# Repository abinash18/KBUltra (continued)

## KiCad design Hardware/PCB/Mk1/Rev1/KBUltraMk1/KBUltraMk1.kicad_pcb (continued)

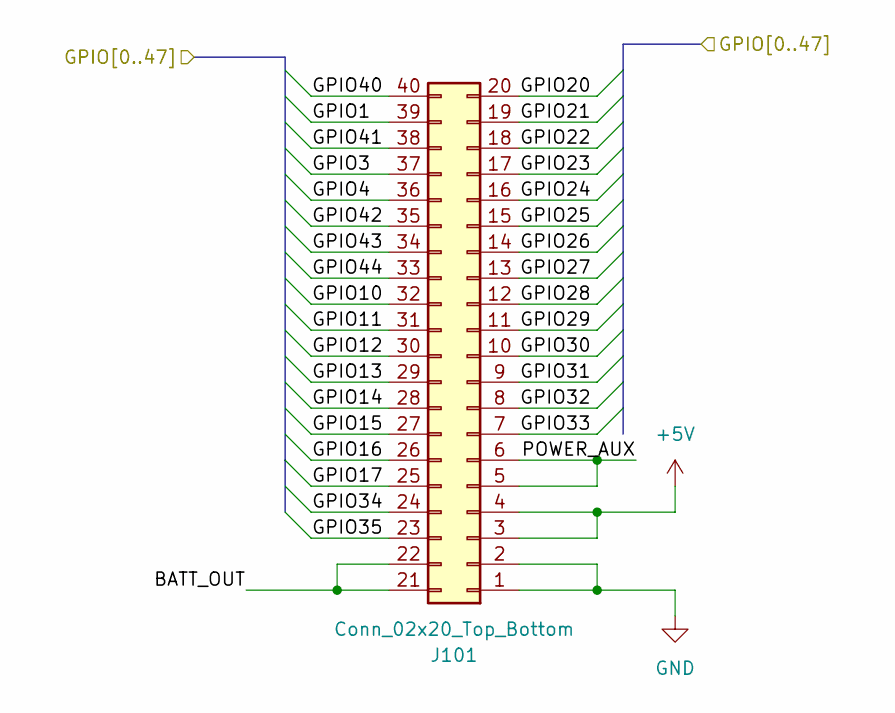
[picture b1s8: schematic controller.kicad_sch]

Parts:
J101: Conn_02x20_Top_Bottom; PinHeader_2x20_P2.54mm_Vertical

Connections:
+5V: J101.3, J101.4; also elsewhere on the board
/Controller/BATT_OUT: J101.21, J101.22
/Controller/GPIO1: J101.39; also elsewhere on the board
/Controller/GPIO3: J101.37; also elsewhere on the board
/Controller/GPIO4: J101.36; also elsewhere on the board
/Controller/GPIO10: J101.32; also elsewhere on the board
/Controller/GPIO11: J101.31; also elsewhere on the board
/Controller/GPIO12: J101.30; also elsewhere on the board
/Controller/GPIO13: J101.29; also elsewhere on the board
/Controller/GPIO14: J101.28; also elsewhere on the board
/Controller/GPIO15: J101.27; also elsewhere on the board
/Controller/GPIO16: J101.26; also elsewhere on the board
/Controller/GPIO17: J101.25; also elsewhere on the board
/Controller/GPIO20: J101.20; also elsewhere on the board
/Controller/GPIO21: J101.19; also elsewhere on the board
/Controller/GPIO22: J101.18; also elsewhere on the board
/Controller/GPIO23: J101.17; also elsewhere on the board
/Controller/GPIO24: J101.16; also elsewhere on the board
/Controller/GPIO25: J101.15; also elsewhere on the board
/Controller/GPIO26: J101.14; also elsewhere on the board
/Controller/GPIO27: J101.13; also elsewhere on the board
/Controller/GPIO28: J101.12; also elsewhere on the board
/Controller/GPIO29: J101.11; also elsewhere on the board
/Controller/GPIO30: J101.10; also elsewhere on the board
/Controller/GPIO31: J101.9; also elsewhere on the board
/Controller/GPIO32: J101.8; also elsewhere on the board
/Controller/GPIO33: J101.7; also elsewhere on the board
/Controller/GPIO34: J101.24; also elsewhere on the board
/Controller/GPIO35: J101.23; also elsewhere on the board
/Controller/GPIO40: J101.40; also elsewhere on the board
/Controller/GPIO41: J101.38; also elsewhere on the board
/Controller/GPIO42: J101.35; also elsewhere on the board
/Controller/GPIO43: J101.34; also elsewhere on the board
/Controller/GPIO44: J101.33; also elsewhere on the board
/Controller/POWER_AUX: J101.5, J101.6
GND: J101.1, J101.2; also elsewhere on the board

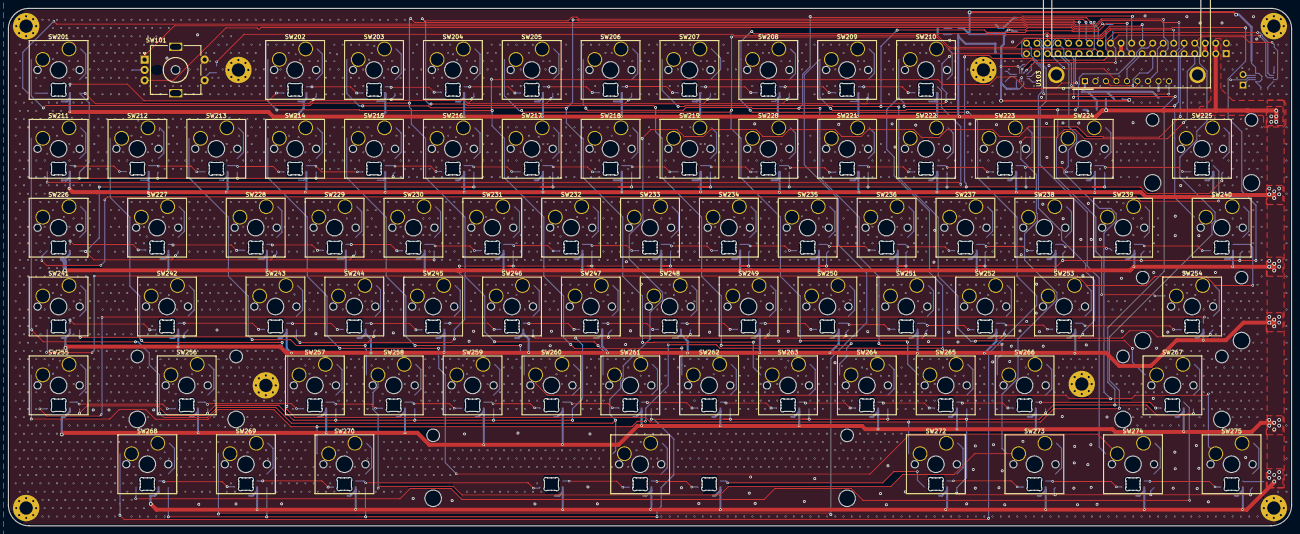
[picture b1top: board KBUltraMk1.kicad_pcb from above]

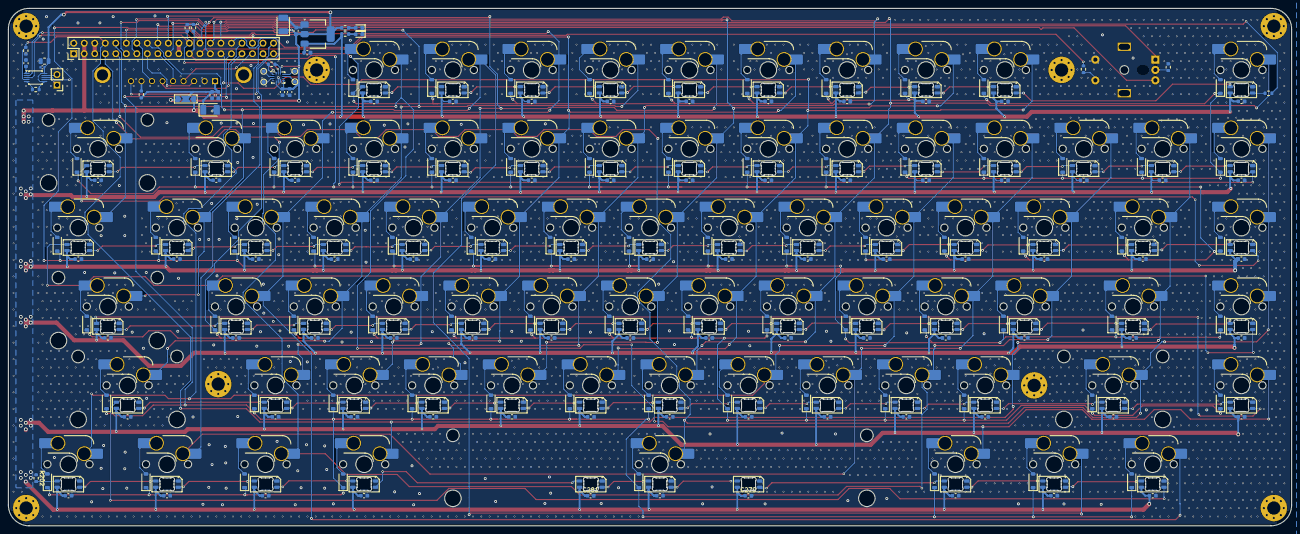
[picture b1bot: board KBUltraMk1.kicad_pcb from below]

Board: 2 copper layers, 310.0 x 125.0 mm, 354 parts (264 on the bottom side), 205 nets.

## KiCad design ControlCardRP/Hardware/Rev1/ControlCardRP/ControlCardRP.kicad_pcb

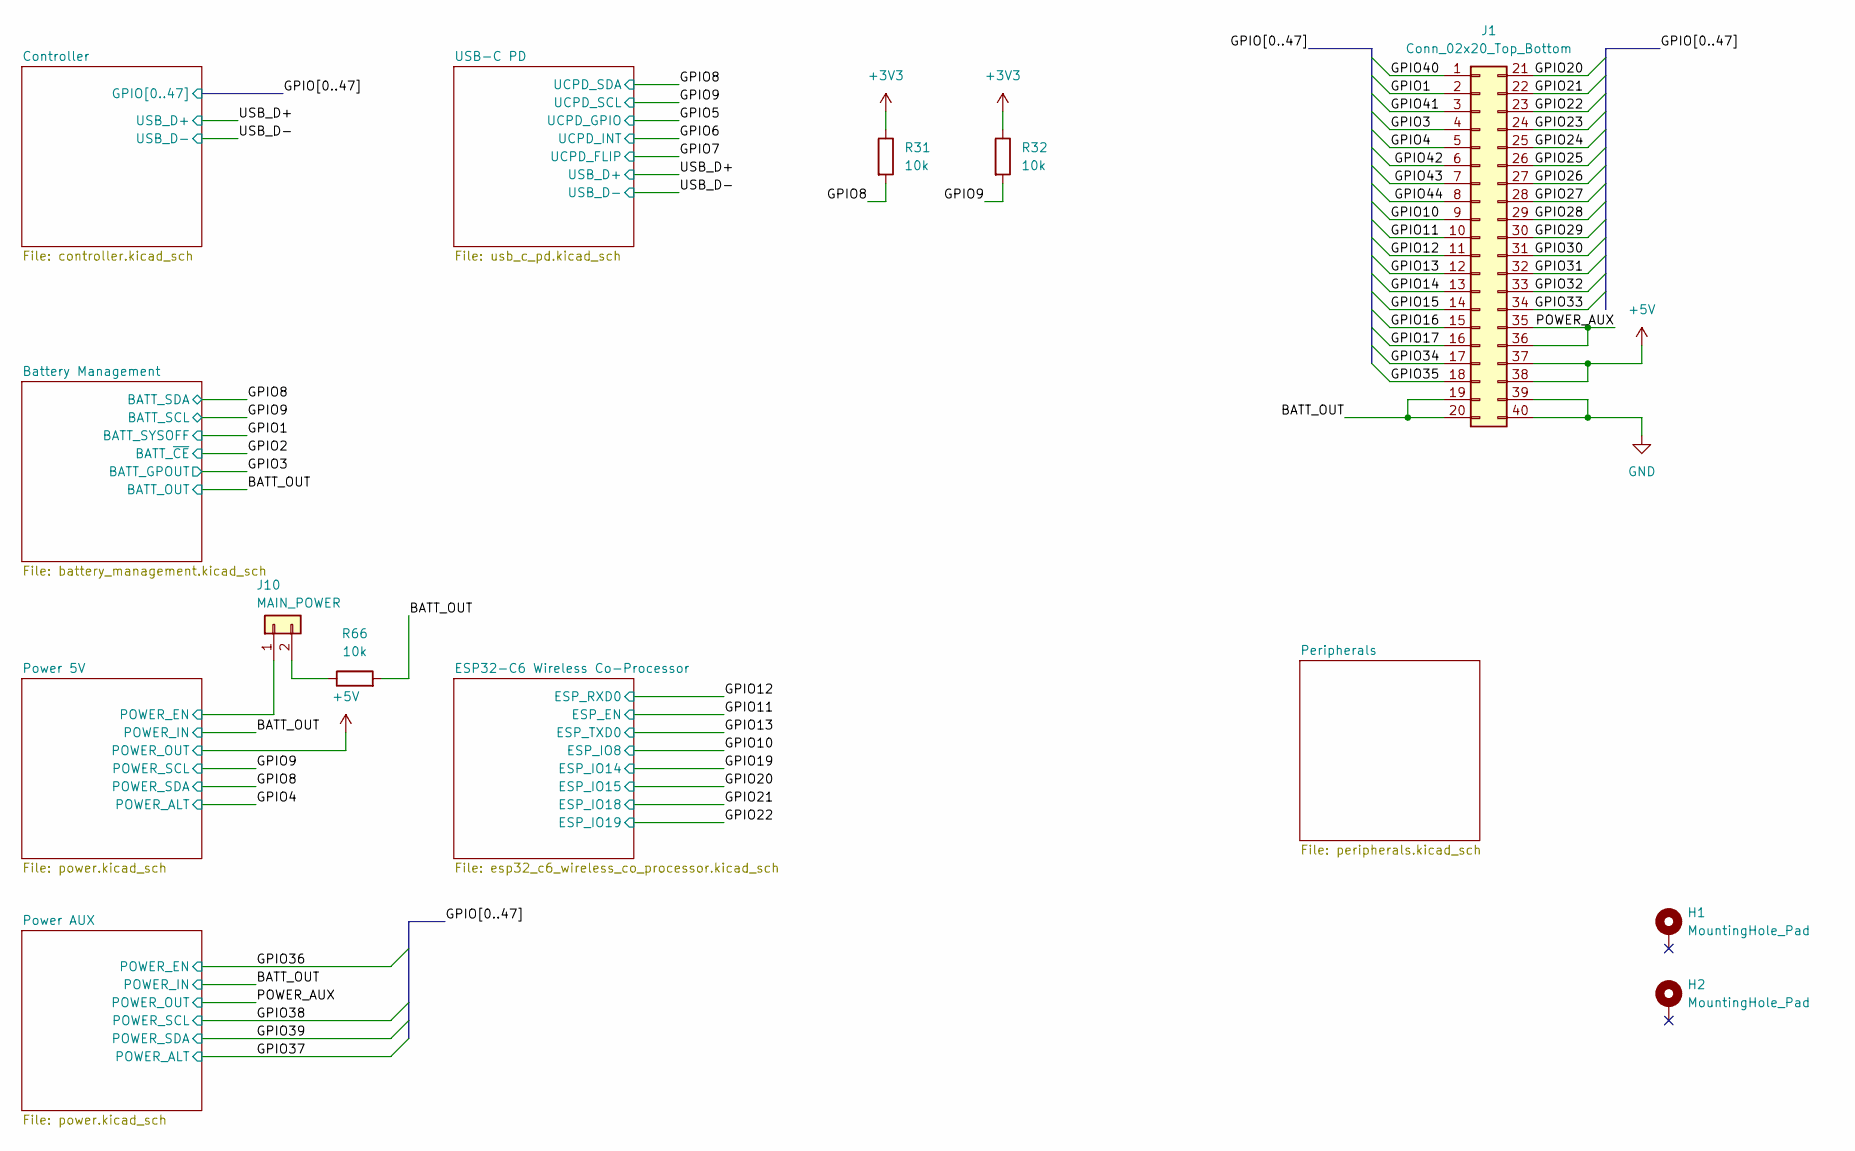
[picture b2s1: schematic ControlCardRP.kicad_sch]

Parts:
H1, H2: MountingHole_Pad; MountingHole_3.2mm_M3_Pad_Via
J1: Conn_02x20_Top_Bottom; PinSocket_2x20_P2.54mm_Vertical_SMD
J10: MAIN_POWER; PinHeader_1x02_P2.54mm_Vertical
R31, R32, R66: 10k; R_0402_1005Metric; LCSC Part # C25744

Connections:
+3V3: R31.1, R32.1; also elsewhere on the board
+5V: J1.37, J1.38; also elsewhere on the board
/BATT_OUT: J1.19, J1.20, R66.2; also elsewhere on the board
/GPIO1: J1.2; also elsewhere on the board
/GPIO3: J1.4; also elsewhere on the board
/GPIO4: J1.5; also elsewhere on the board
/GPIO8: R31.2; also elsewhere on the board
/GPIO9: R32.2; also elsewhere on the board
/GPIO10: J1.9; also elsewhere on the board
/GPIO11: J1.10; also elsewhere on the board
/GPIO12: J1.11; also elsewhere on the board
/GPIO13: J1.12; also elsewhere on the board
/GPIO14: J1.13; also elsewhere on the board
/GPIO15: J1.14; also elsewhere on the board
/GPIO16: J1.15; also elsewhere on the board
/GPIO17: J1.16; also elsewhere on the board
/GPIO20: J1.21; also elsewhere on the board
/GPIO21: J1.22; also elsewhere on the board
/GPIO22: J1.23; also elsewhere on the board
/GPIO23: J1.24; also elsewhere on the board
/GPIO24: J1.25; also elsewhere on the board
/GPIO25: J1.26; also elsewhere on the board
/GPIO26: J1.27; also elsewhere on the board
/GPIO27: J1.28; also elsewhere on the board
/GPIO28: J1.29; also elsewhere on the board
/GPIO29: J1.30; also elsewhere on the board
/GPIO30: J1.31; also elsewhere on the board
/GPIO31: J1.32; also elsewhere on the board
/GPIO32: J1.33; also elsewhere on the board
/GPIO33: J1.34; also elsewhere on the board
/GPIO34: J1.17; also elsewhere on the board
/GPIO35: J1.18; also elsewhere on the board
/GPIO40: J1.1; also elsewhere on the board
/GPIO41: J1.3; also elsewhere on the board
/GPIO42: J1.6; also elsewhere on the board
/GPIO43: J1.7; also elsewhere on the board
/GPIO44: J1.8; also elsewhere on the board
/POWER_AUX: J1.35, J1.36; also elsewhere on the board
/Power 5V/POWER_EN: J10.1; also elsewhere on the board
GND: J1.39, J1.40; also elsewhere on the board
unnamed: J10.2, R66.1

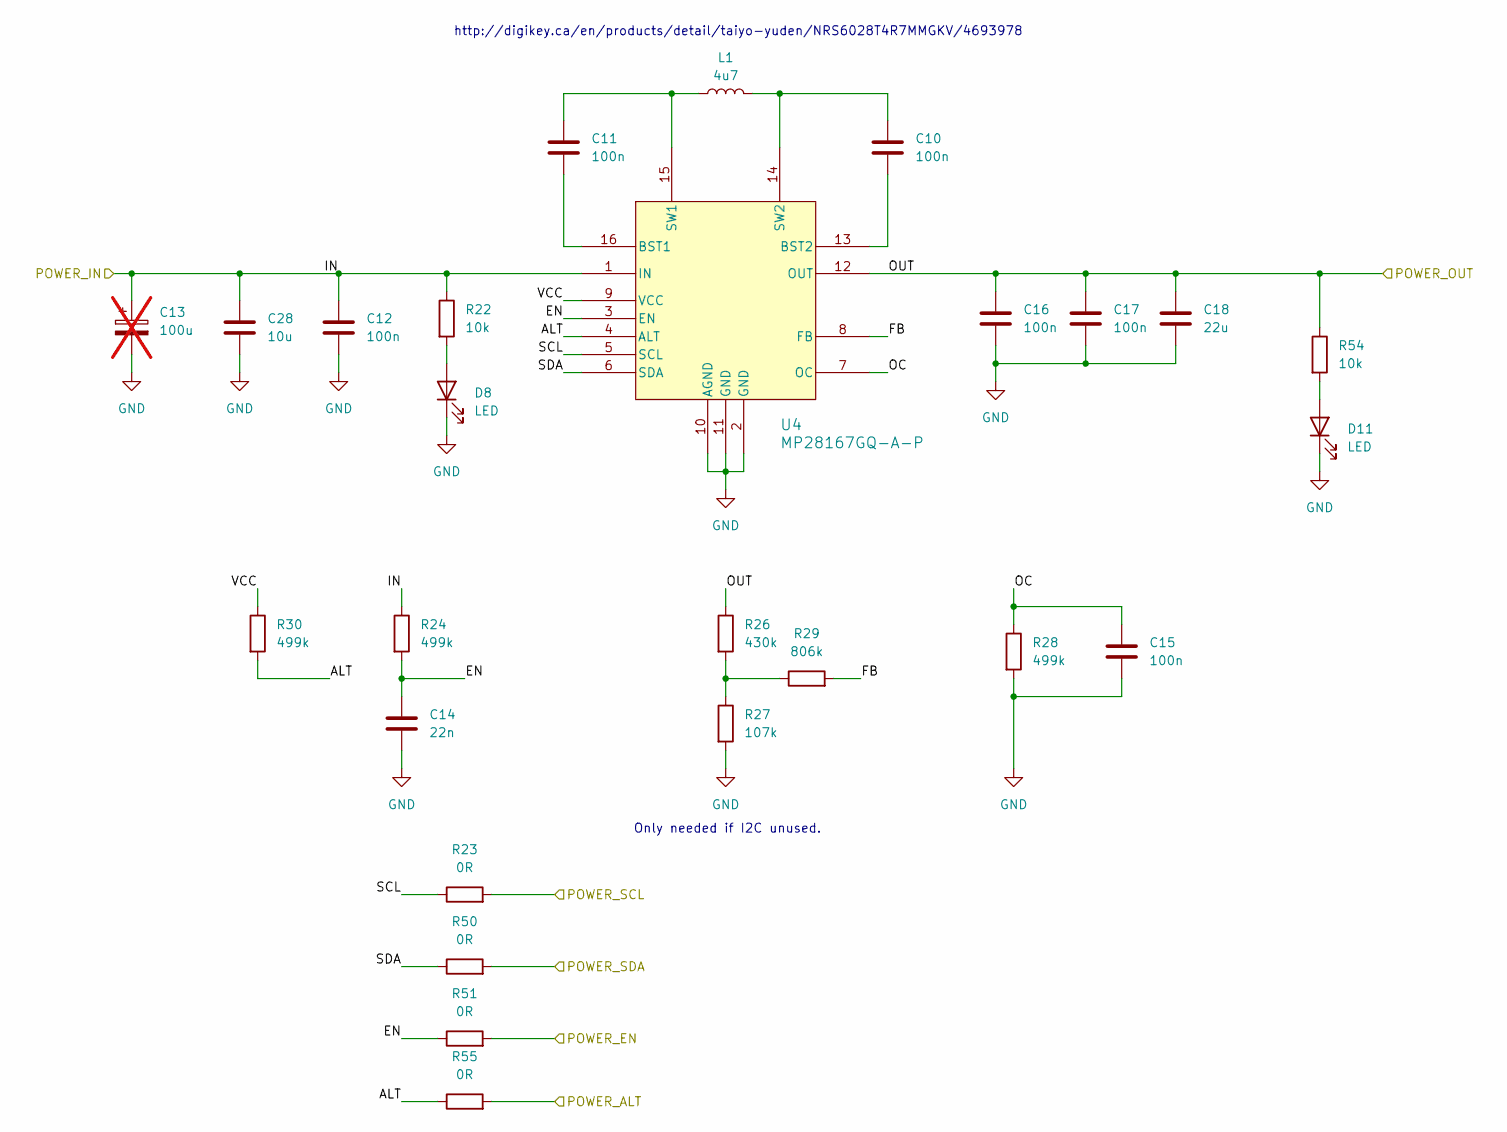
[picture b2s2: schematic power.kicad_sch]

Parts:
C10, C11, C12, C16, C17: 100n; C_0402_1005Metric; LCSC Part # C307331
C13: 100u; CP_Elec_5x5.4; not fitted
C14: 22n; C_0402_1005Metric; LCSC Part # C1532
C15: 100n; C_0402_1005Metric; LCSC Part # C1525
C18: 22u; C_1206_3216Metric; LCSC Part # C12891
C28: 10u; C_0603_1608Metric; LCSC Part # C96446
D8, D11: LED; LED_0603_1608Metric
L1: 4u7; L_Taiyo-Yuden_NR-60xx
R22, R54: 10k; R_0402_1005Metric; LCSC Part # C25744
R23, R50, R51, R55: 0R; R_0402_1005Metric; LCSC Part # C17168
R24, R28, R30: 499k; R_0402_1005Metric; LCSC Part # C25778
R26: 430k; R_0603_1608Metric; LCSC Part # C25969
R27: 107k; R_0603_1608Metric; LCSC Part # C25805
R29: 806k; R_0603_1608Metric; LCSC Part # C23240
U4: MP28167GQ-A-P; QFN-16_MP28167_MNP

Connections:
+5V: C16.1, C17.1, C18.1, R26.1, R54.1, U4.12 (OUT); also elsewhere on the board
/BATT_OUT: C12.1, C13.1, C28.1, R22.1, R24.1, U4.1 (IN); also elsewhere on the board
/GPIO4: R55.2; also elsewhere on the board
/GPIO8: R50.2; also elsewhere on the board
/GPIO9: R23.2; also elsewhere on the board
/Power 5V/ALT: R30.2, R55.1, U4.4 (ALT)
/Power 5V/EN: C14.1, R24.2, R51.1, U4.3 (EN)
/Power 5V/FB: R29.2, U4.8 (FB)
/Power 5V/OC: C15.1, R28.1, U4.7 (OC)
/Power 5V/POWER_EN: R51.2; also elsewhere on the board
/Power 5V/SCL: R23.1, U4.5 (SCL)
/Power 5V/SDA: R50.1, U4.6 (SDA)
/Power 5V/VCC: R30.1, U4.9 (VCC)
GND: C12.2, C13.2, C14.2, C15.2, C16.2, C17.2, C18.2, C28.2, D8.1 (K), D11.1 (K), R27.2, R28.2, U4.2 (GND), U4.10 (AGND), U4.11 (GND); also elsewhere on the board
unnamed: D8.2 (A), R22.2
unnamed: D11.2 (A), R54.2
unnamed: R26.2, R27.1, R29.1
unnamed: C11.2, U4.16 (BST1)
unnamed: C10.2, U4.13 (BST2)
unnamed: C11.1, L1.1, U4.15 (SW1)
unnamed: C10.1, L1.2, U4.14 (SW2)

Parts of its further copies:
C26: 100u; CP_Elec_5x5.4; not fitted
C27, C31, C32, C33, C34: 100n; C_0402_1005Metric; LCSC Part # C307331
C29: 10u; C_0603_1608Metric; LCSC Part # C96446
C30: 22n; C_0402_1005Metric; LCSC Part # C1532
C35: 100n; C_0402_1005Metric; LCSC Part # C1525
C36: 22u; C_1206_3216Metric; LCSC Part # C12891
D9, D12: LED; LED_0603_1608Metric
L2: 4u7; L_Taiyo-Yuden_NR-60xx
R52, R53, R64: 499k; R_0402_1005Metric; LCSC Part # C25778
R56, R65: 10k; R_0402_1005Metric; LCSC Part # C25744
R57, R58, R59, R60: 0R; R_0402_1005Metric; LCSC Part # C17168
R61: 430k; R_0603_1608Metric; LCSC Part # C25969
R62: 107k; R_0603_1608Metric; LCSC Part # C25805
R63: 806k; R_0603_1608Metric; LCSC Part # C23240
U8: MP28167GQ-A-P; QFN-16_MP28167_MNP

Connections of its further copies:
/BATT_OUT: C26.1, C27.1, C29.1, R53.1, R56.1, U8.1 (IN); also elsewhere on the board
/GPIO36: R59.2; also elsewhere on the board
/GPIO37: R60.2; also elsewhere on the board
/GPIO38: R57.2; also elsewhere on the board
/GPIO39: R58.2; also elsewhere on the board
/POWER_AUX: C33.1, C34.1, C36.1, R61.1, R65.1, U8.12 (OUT); also elsewhere on the board
/Power AUX/ALT: R52.2, R60.1, U8.4 (ALT)
/Power AUX/EN: C30.1, R53.2, R59.1, U8.3 (EN)
/Power AUX/FB: R63.2, U8.8 (FB)
/Power AUX/OC: C35.1, R64.1, U8.7 (OC)
/Power AUX/SCL: R57.1, U8.5 (SCL)
/Power AUX/SDA: R58.1, U8.6 (SDA)
/Power AUX/VCC: R52.1, U8.9 (VCC)
GND: C26.2, C27.2, C29.2, C30.2, C33.2, C34.2, C35.2, C36.2, D9.1 (K), D12.1 (K), R62.2, R64.2, U8.2 (GND), U8.10 (AGND), U8.11 (GND); also elsewhere on the board
unnamed: D9.2 (A), R56.2
unnamed: D12.2 (A), R65.2
unnamed: R61.2, R62.1, R63.1
unnamed: C31.2, U8.16 (BST1)
unnamed: C32.2, U8.13 (BST2)
unnamed: C31.1, L2.1, U8.15 (SW1)
unnamed: C32.1, L2.2, U8.14 (SW2)

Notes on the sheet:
http://digikey.ca/en/products/detail/taiyo-yuden/NRS6028T4R7MMGKV/4693978
Only needed if I2C unused.

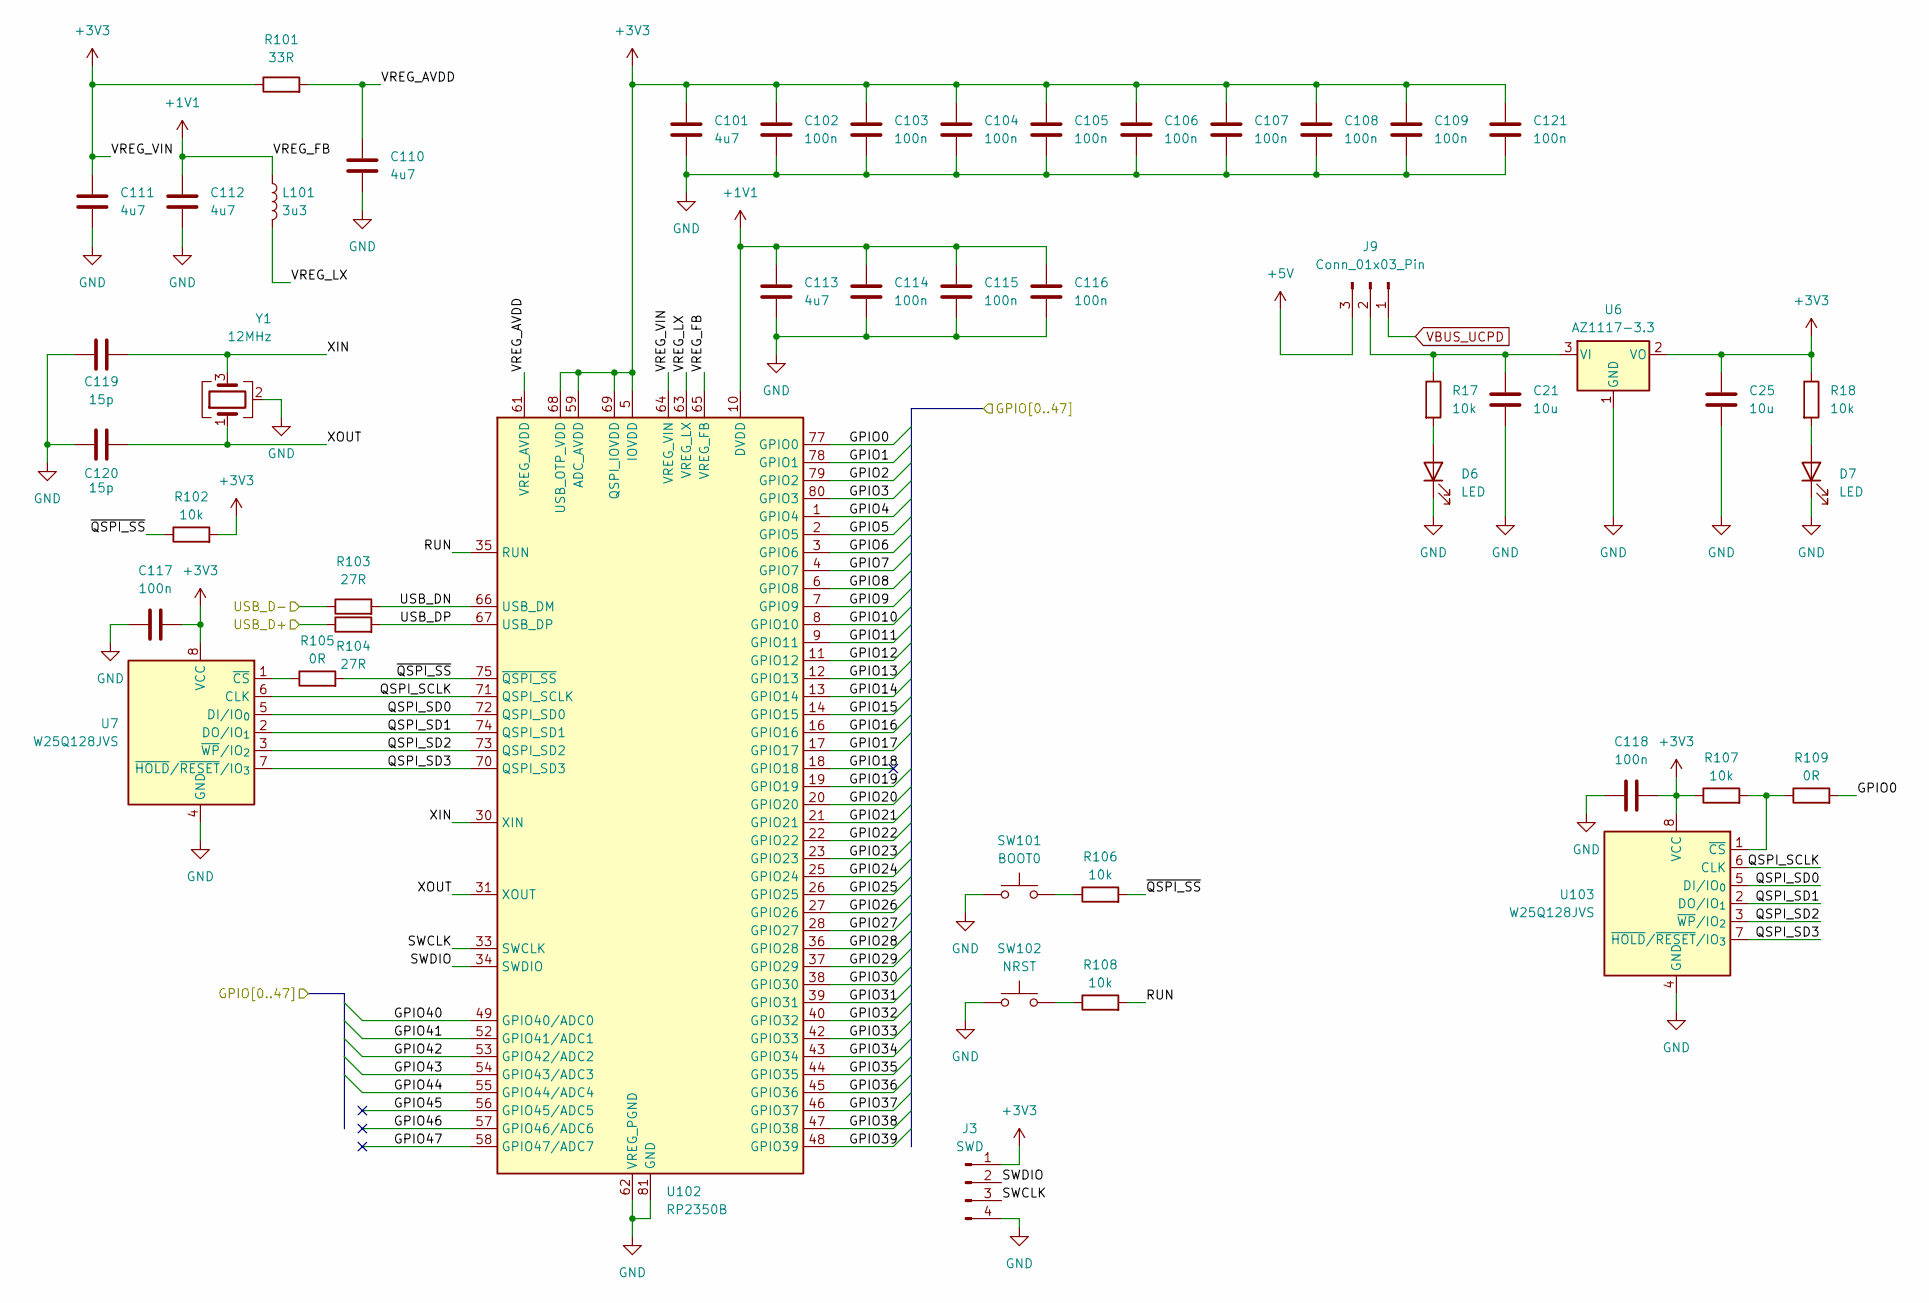
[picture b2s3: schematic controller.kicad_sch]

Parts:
C21, C25: 10u; C_0603_1608Metric; LCSC Part # C96446
C101, C110, C111, C112, C113: 4u7; C_0402_1005Metric; LCSC Part # C23733
C102, C103, C104, C105, C106, C107, C108, C109, C114, C115, C116, C117, C118, C121: 100n; C_0402_1005Metric; LCSC Part # C1525
C119, C120: 15p; C_0402_1005Metric; LCSC Part # C1548
D6, D7: LED; LED_0603_1608Metric
J3: SWD; PinHeader_1x04_P2.54mm_Vertical
J9: Conn_01x03_Pin; PinHeader_1x03_P1.27mm_Vertical
L101: 3u3; AOTA-B201610S3R3-101-T
R17, R18, R102, R106, R107, R108: 10k; R_0402_1005Metric; LCSC Part # C25744
R101: 33R; R_0402_1005Metric; LCSC Part # C25105
R103, R104: 27R; R_0603_1608Metric; LCSC Part # C25190
R105, R109: 0R; R_0402_1005Metric; LCSC Part # C17168
SW101: BOOT0; SW_SPST_PTS810
SW102: NRST; SW_SPST_PTS810
U6: AZ1117-3.3; SOT-89-3
U7, U103: W25Q128JVS; SOIC-8_5.3x5.3mm_P1.27mm
U102: RP2350B; QFN-80-1EP_10x10mm_P0.4mm_EP3.4x3.4mm
Y1: 12MHz; Crystal_SMD_3225-4Pin_3.2x2.5mm

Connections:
+1V1: C112.1, C113.1, C114.1, C115.1, C116.1, L101.1, U102.10 (DVDD), U102.32 (DVDD), U102.51 (DVDD), U102.65 (VREG_FB)
+3V3: C25.1, C101.1, C102.1, C103.1, C104.1, C105.1, C106.1, C107.1, C108.1, C109.1, C111.1, C117.2, C118.2, C121.1, J3.1, R18.1, R101.1, R102.2, R107.1, U6.2 (VO), U7.8 (VCC), U102.5 (IOVDD), U102.15 (IOVDD), U102.24 (IOVDD), U102.29 (IOVDD), U102.41 (IOVDD), U102.50 (IOVDD), U102.59 (ADC_AVDD), U102.60 (IOVDD), U102.64 (VREG_VIN), U102.68 (USB_OTP_VDD), U102.69 (QSPI_IOVDD), U102.76 (IOVDD), U103.8 (VCC); also elsewhere on the board
+5V: J9.3; also elsewhere on the board
/Controller/QSPI_SCLK: U7.6 (CLK), U102.71 (QSPI_SCLK), U103.6 (CLK)
/Controller/QSPI_SD0: U7.5 (DI/IO_{0}), U102.72 (QSPI_SD0), U103.5 (DI/IO_{0})
/Controller/QSPI_SD1: U7.2 (DO/IO_{1}), U102.74 (QSPI_SD1), U103.2 (DO/IO_{1})
/Controller/QSPI_SD2: U7.3 (~WP/IO_{2}), U102.73 (QSPI_SD2), U103.3 (~WP/IO_{2})
/Controller/QSPI_SD3: U7.7 (~HOLD/~RESET/IO_{3}), U102.70 (QSPI_SD3), U103.7 (~HOLD/~RESET/IO_{3})
/Controller/RUN: R108.2, U102.35 (RUN)
/Controller/SWCLK: J3.3, U102.33 (SWCLK)
/Controller/SWDIO: J3.2, U102.34 (SWDIO)
/Controller/USB_DN: R103.2, U102.66 (USB_DM)
/Controller/USB_DP: R104.2, U102.67 (USB_DP)
/Controller/VREG_AVDD: C110.1, R101.2, U102.61 (VREG_AVDD)
/Controller/VREG_LX: L101.2, U102.63 (VREG_LX)
/Controller/XIN: C119.2, U102.30 (XIN), Y1.3
/Controller/XOUT: C120.1, U102.31 (XOUT), Y1.1
/Controller/~QSPI_SS: R102.1, R105.2, R106.2, U102.75 (~QSPI_SS)
/GPIO0: R109.2, U102.77 (GPIO0)
/GPIO1: U102.78 (GPIO1); also elsewhere on the board
/GPIO2: U102.79 (GPIO2); also elsewhere on the board
/GPIO3: U102.80 (GPIO3); also elsewhere on the board
/GPIO4: U102.1 (GPIO4); also elsewhere on the board
/GPIO5: U102.2 (GPIO5); also elsewhere on the board
/GPIO6: U102.3 (GPIO6); also elsewhere on the board
/GPIO7: U102.4 (GPIO7); also elsewhere on the board
/GPIO8: U102.6 (GPIO8); also elsewhere on the board
/GPIO9: U102.7 (GPIO9); also elsewhere on the board
/GPIO10: U102.8 (GPIO10); also elsewhere on the board
/GPIO11: U102.9 (GPIO11); also elsewhere on the board
/GPIO12: U102.11 (GPIO12); also elsewhere on the board
/GPIO13: U102.12 (GPIO13); also elsewhere on the board
/GPIO14: U102.13 (GPIO14); also elsewhere on the board
/GPIO15: U102.14 (GPIO15); also elsewhere on the board
/GPIO16: U102.16 (GPIO16); also elsewhere on the board
/GPIO17: U102.17 (GPIO17); also elsewhere on the board
/GPIO18: U102.18 (GPIO18)
/GPIO19: U102.19 (GPIO19); also elsewhere on the board
/GPIO20: U102.20 (GPIO20); also elsewhere on the board
/GPIO21: U102.21 (GPIO21); also elsewhere on the board
/GPIO22: U102.22 (GPIO22); also elsewhere on the board
/GPIO23: U102.23 (GPIO23); also elsewhere on the board
/GPIO24: U102.25 (GPIO24); also elsewhere on the board
/GPIO25: U102.26 (GPIO25); also elsewhere on the board
/GPIO26: U102.27 (GPIO26); also elsewhere on the board
/GPIO27: U102.28 (GPIO27); also elsewhere on the board
/GPIO28: U102.36 (GPIO28); also elsewhere on the board
/GPIO29: U102.37 (GPIO29); also elsewhere on the board
/GPIO30: U102.38 (GPIO30); also elsewhere on the board
/GPIO31: U102.39 (GPIO31); also elsewhere on the board
/GPIO32: U102.40 (GPIO32); also elsewhere on the board
/GPIO33: U102.42 (GPIO33); also elsewhere on the board
/GPIO34: U102.43 (GPIO34); also elsewhere on the board
/GPIO35: U102.44 (GPIO35); also elsewhere on the board
/GPIO36: U102.45 (GPIO36); also elsewhere on the board
/GPIO37: U102.46 (GPIO37); also elsewhere on the board
/GPIO38: U102.47 (GPIO38); also elsewhere on the board
/GPIO39: U102.48 (GPIO39); also elsewhere on the board
/GPIO40: U102.49 (GPIO40/ADC0); also elsewhere on the board
/GPIO41: U102.52 (GPIO41/ADC1); also elsewhere on the board
/GPIO42: U102.53 (GPIO42/ADC2); also elsewhere on the board
/GPIO43: U102.54 (GPIO43/ADC3); also elsewhere on the board
/GPIO44: U102.55 (GPIO44/ADC4); also elsewhere on the board
/GPIO45: U102.56 (GPIO45/ADC5)
/GPIO46: U102.57 (GPIO46/ADC6)
/GPIO47: U102.58 (GPIO47/ADC7)
/USB_D+: R104.1; also elsewhere on the board
/USB_D-: R103.1; also elsewhere on the board
GND: C21.2, C25.2, C101.2, C102.2, C103.2, C104.2, C105.2, C106.2, C107.2, C108.2, C109.2, C110.2, C111.2, C112.2, C113.2, C114.2, C115.2, C116.2, C117.1, C118.1, C119.1, C120.2, C121.2, D6.1 (K), D7.1 (K), J3.4, SW101.1, SW102.1, U6.1 (GND), U7.4 (GND), U102.62 (VREG_PGND), U102.81 (GND), U103.4 (GND), Y1.2 (G), Y1.4 (G); also elsewhere on the board
unnamed: D6.2 (A), R17.2
unnamed: D7.2 (A), R18.2
unnamed: C21.1, J9.2, R17.1, U6.3 (VI)
unnamed: R106.1, SW101.2
unnamed: R108.1, SW102.2
unnamed: R105.1, U7.1 (~CS)
unnamed: R107.2, R109.1, U103.1 (~CS)
VBUS_UCPD: J9.1; also elsewhere on the board

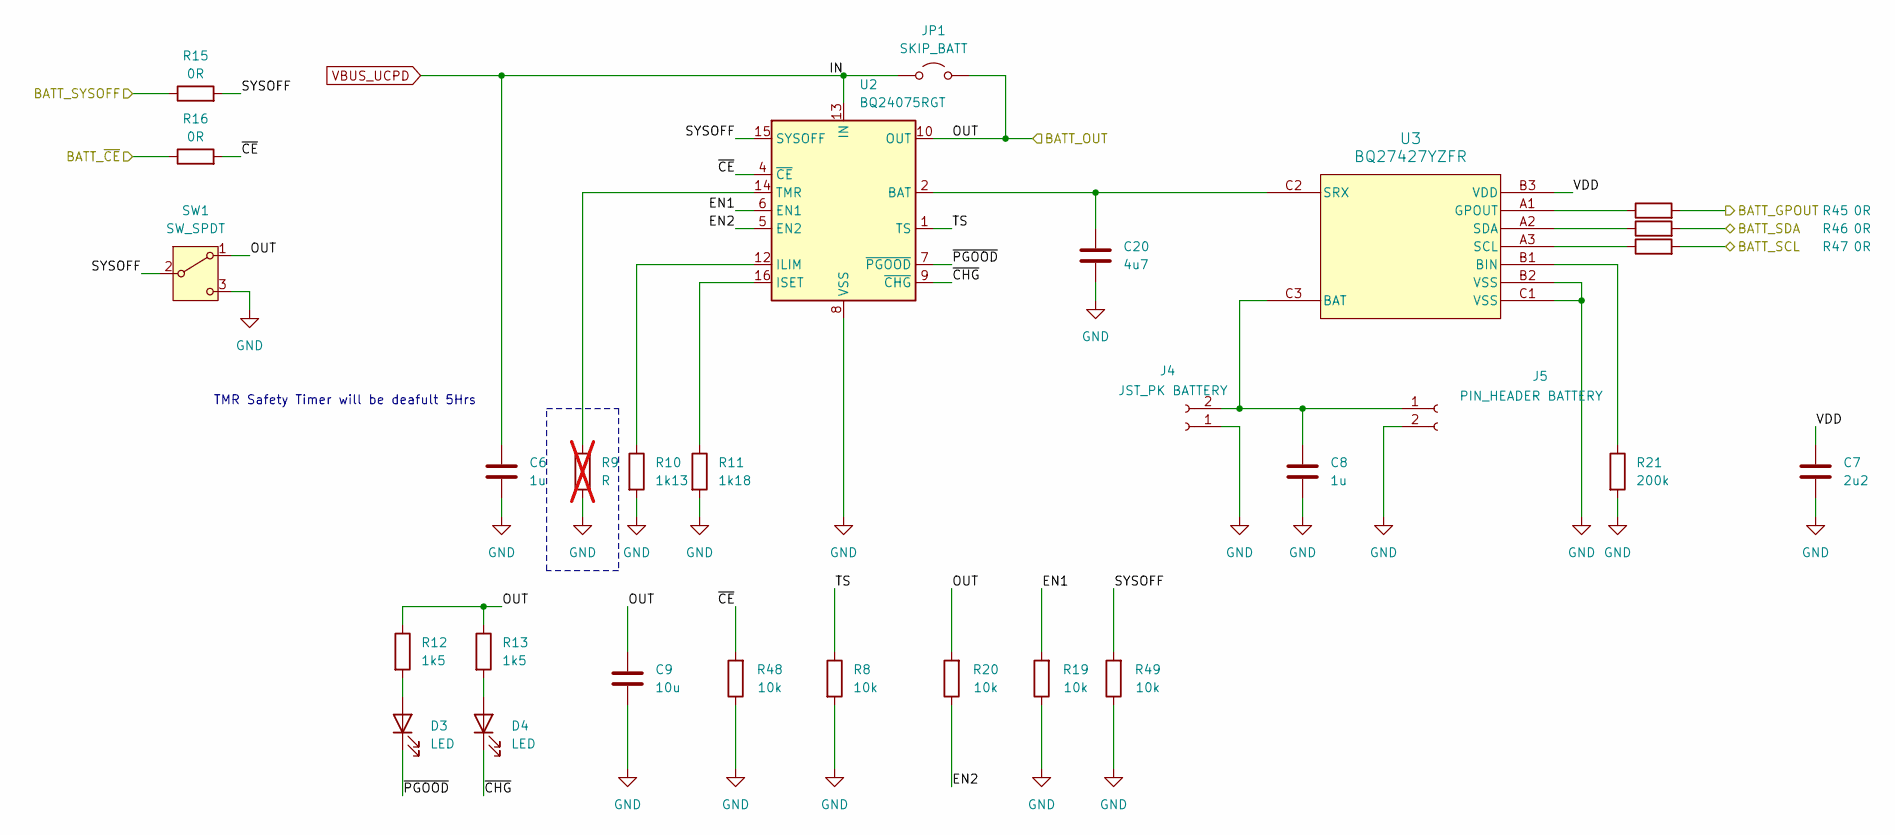
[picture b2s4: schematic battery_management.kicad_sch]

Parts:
C6, C8: 1u; C_0603_1608Metric; LCSC Part # C15849
C7: 2u2; C_0603_1608Metric; LCSC Part # C12530
C9: 10u; C_0603_1608Metric; LCSC Part # C96446
C20: 4u7; C_0402_1005Metric; LCSC Part # C23733
D3, D4: LED; LED_0603_1608Metric
J4: JST_PK BATTERY; JST_PH_S2B-PH-K_1x02_P2.00mm_Horizontal
J5: PIN_HEADER BATTERY; PinSocket_1x02_P2.54mm_Vertical
JP1: SKIP_BATT; SolderJumper-2_P1.3mm_Open_TrianglePad1.0x1.5mm
R8, R19, R20, R48, R49: 10k; R_0402_1005Metric; LCSC Part # C25744
R9: R; R_0402_1005Metric; not fitted
R10: 1k13; R_0402_1005Metric; LCSC Part # C25862
R11: 1k18; R_0402_1005Metric; LCSC Part # C25867
R12, R13: 1k5; R_0402_1005Metric; LCSC Part # C25867
R15, R16, R45, R46, R47: 0R; R_0402_1005Metric; LCSC Part # C17168
R21: 200k; R_0402_1005Metric; LCSC Part # C25764
SW1: SW_SPDT; SW_SPDT_PCM12
U2: BQ24075RGT; VQFN-16-1EP_3x3mm_P0.5mm_EP1.6x1.6mm
U3: BQ27427YZFR; DSBGA9-YZF_TEX

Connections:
/BATT_OUT: C9.1, JP1.2 (B), R12.1, R13.1, R20.2, SW1.1 (A), U2.10 (OUT), U2.11 (OUT); also elsewhere on the board
/Battery Management/EN1: R19.2, U2.6 (EN1)
/Battery Management/EN2: R20.1, U2.5 (EN2)
/Battery Management/SYSOFF: R15.2, R49.2, SW1.2 (B), U2.15 (SYSOFF)
/Battery Management/TS: R8.1, U2.1 (TS)
/Battery Management/VDD: C7.1, U3.B3 (VDD)
/Battery Management/~CE: R16.2, R48.2, U2.4 (~CE)
/Battery Management/~CHG: D4.1 (K), U2.9 (~CHG)
/Battery Management/~PGOOD: D3.1 (K), U2.7 (~PGOOD)
/GPIO1: R15.1; also elsewhere on the board
/GPIO2: R16.1; also elsewhere on the board
/GPIO3: R45.2; also elsewhere on the board
/GPIO8: R46.2; also elsewhere on the board
/GPIO9: R47.2; also elsewhere on the board
GND: C6.2, C7.2, C8.2, C9.2, C20.2, J4.1, J5.2, R8.2, R9.2, R10.2, R11.2, R19.1, R21.2, R48.1, R49.1, SW1.3 (C), U2.8 (VSS), U2.17 (VSS), U3.B2 (VSS), U3.C1 (VSS); also elsewhere on the board
unnamed: D3.2 (A), R12.2
unnamed: D4.2 (A), R13.2
unnamed: C8.1, J4.2, J5.1, U3.C3 (BAT)
unnamed: R10.1, U2.12 (ILIM)
unnamed: R11.1, U2.16 (ISET)
unnamed: R9.1, U2.14 (TMR)
unnamed: R21.1, U3.B1 (BIN)
unnamed: R45.1, U3.A1 (GPOUT)
unnamed: R47.1, U3.A3 (SCL)
unnamed: R46.1, U3.A2 (SDA)
unnamed: C20.1, U2.2 (BAT), U2.3 (BAT), U3.C2 (SRX)
VBUS_UCPD: C6.1, JP1.1 (A), U2.13 (IN); also elsewhere on the board

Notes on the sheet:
TMR Safety Timer will be deafult 5Hrs

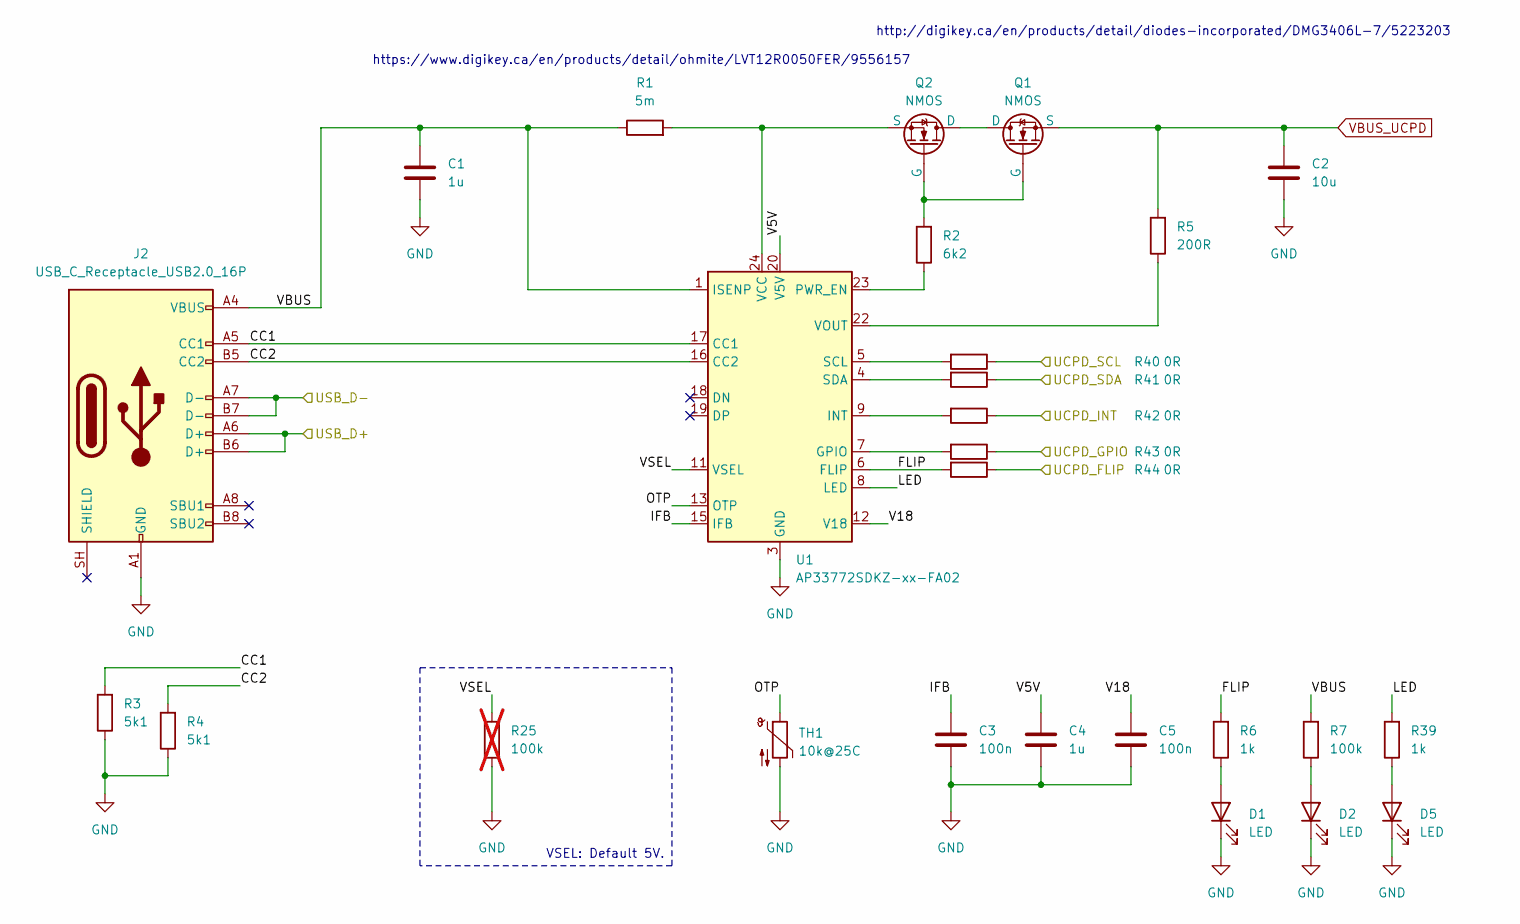
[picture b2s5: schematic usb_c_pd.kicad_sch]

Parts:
C1, C4: 1u; C_0603_1608Metric; LCSC Part # C15849
C2: 10u; C_0603_1608Metric; LCSC Part # C96446
C3, C5: 100n; C_0402_1005Metric; LCSC Part # C307331
D1, D2, D5: LED; LED_0603_1608Metric
J2: USB_C_Receptacle_USB2.0_16P; USB_C_Receptacle_GCT_USB4105-xx-A_16P_TopMnt_Horizontal
Q1, Q2: NMOS; SOT-23-3
R1: 5m; R_1206_3216Metric
R2: 6k2; R_0402_1005Metric; LCSC Part # C25905
R3, R4: 5k1; R_0402_1005Metric; LCSC Part # C25905
R5: 200R; R_0402_1005Metric; LCSC Part # C25087
R6, R39: 1k; R_0402_1005Metric; LCSC Part # C11702
R7: 100k; R_0402_1005Metric; LCSC Part # C25741
R25: 100k; R_0402_1005Metric; LCSC Part # C25741; not fitted
R40, R41, R42, R43, R44: 0R; R_0402_1005Metric; LCSC Part # C17168
TH1: 10k@25C; R_0603_1608Metric
U1: AP33772SDKZ-xx-FA02; Texas_RTW_WQFN-24-1EP_4x4mm_P0.5mm_EP2.7x2.7mm

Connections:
/GPIO5: R43.1; also elsewhere on the board
/GPIO6: R42.1; also elsewhere on the board
/GPIO7: R44.1; also elsewhere on the board
/GPIO8: R41.1; also elsewhere on the board
/GPIO9: R40.1; also elsewhere on the board
/USB-C PD/CC1: J2.A5 (CC1), R3.2, U1.17 (CC1)
/USB-C PD/CC2: J2.B5 (CC2), R4.2, U1.16 (CC2)
/USB-C PD/FLIP: R6.2, R44.2, U1.6 (FLIP)
/USB-C PD/IFB: C3.1, U1.15 (IFB)
/USB-C PD/LED: R39.2, U1.8 (LED)
/USB-C PD/OTP: TH1.1, U1.13 (OTP)
/USB-C PD/V5V: C4.1, U1.20 (V5V)
/USB-C PD/V18: C5.1, U1.12 (V18)
/USB-C PD/VBUS: C1.1, J2.A4 (VBUS), J2.A9 (VBUS), J2.B4 (VBUS), J2.B9 (VBUS), R1.1, R7.2, U1.1 (ISENP)
/USB-C PD/VSEL: R25.2, U1.11 (VSEL)
/USB_D+: J2.A6 (D+), J2.B6 (D+); also elsewhere on the board
/USB_D-: J2.A7 (D-), J2.B7 (D-); also elsewhere on the board
GND: C1.2, C2.2, C3.2, C4.2, C5.2, D1.1 (K), D2.1 (K), D5.1 (K), J2.A1 (GND), J2.A12 (GND), J2.B1 (GND), J2.B12 (GND), R3.1, R4.1, R25.1, TH1.2, U1.3 (GND), U1.25 (GND); also elsewhere on the board
unnamed: D1.2 (A), R6.1
unnamed: D2.2 (A), R7.1
unnamed: D5.2 (A), R39.1
unnamed: Q1.1 (D), Q2.1 (D)
unnamed: Q1.2 (G), Q2.2 (G), R2.2
unnamed: Q2.3 (S), R1.2, U1.24 (VCC)
unnamed: R43.2, U1.7 (GPIO)
unnamed: R42.2, U1.9 (INT)
unnamed: R2.1, U1.23 (PWR_EN)
unnamed: R40.2, U1.5 (SCL)
unnamed: R41.2, U1.4 (SDA)
unnamed: R5.1, U1.22 (VOUT)
VBUS_UCPD: C2.1, Q1.3 (S), R5.2; also elsewhere on the board

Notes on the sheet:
http://digikey.ca/en/products/detail/diodes-incorporated/DMG3406L-7/5223203
VSEL: Default 5V.
https://www.digikey.ca/en/products/detail/ohmite/LVT12R0050FER/9556157
